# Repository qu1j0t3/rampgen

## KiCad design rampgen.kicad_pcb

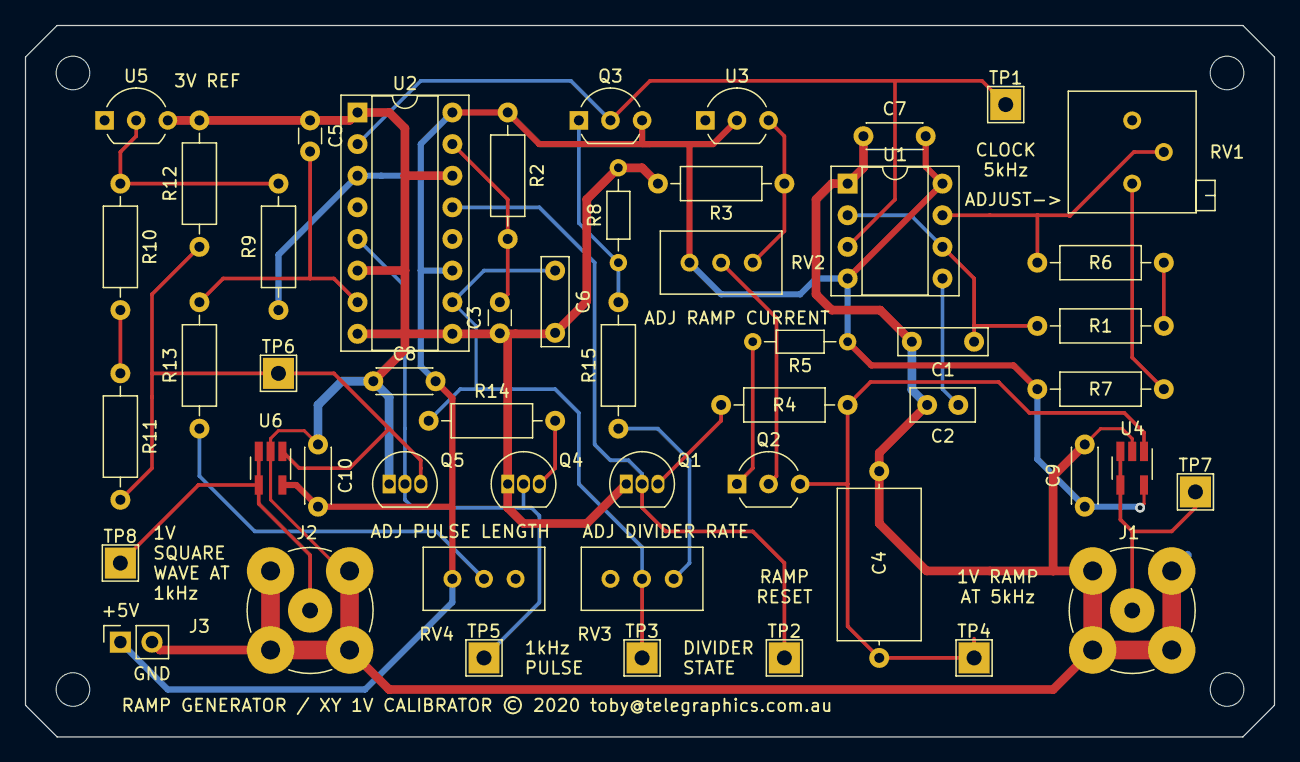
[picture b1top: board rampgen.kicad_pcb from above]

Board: 2 copper layers, 100.3 x 57.2 mm, 55 parts (0 on the bottom side), 27 nets.

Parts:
C1: 10n FILM; C_Rect_L7.0mm_W2.0mm_P5.00mm
C2: 100n; C_Disc_D5.0mm_W2.5mm_P2.50mm
C3, C5: 1n CER; C_Disc_D3.0mm_W1.6mm_P2.50mm
C4: 1.5n STYRENE; C_Axial_L12.0mm_D6.5mm_P15.00mm_Horizontal
C6: 100n FILM; C_Rect_L7.0mm_W2.0mm_P5.00mm
C7, C8, C9, C10: .01u; C_Disc_D4.3mm_W1.9mm_P5.00mm
H1, H2, H3, H4: MountingHole; MountingHole_2.7mm_M2.5
J1: RAMP_OUT; BNC_TEConnectivity_1478204_Vertical
J2: 1V_OUT; BNC_TEConnectivity_1478204_Vertical
J3: Conn_01x02_Female; PinSocket_1x02_P2.54mm_Vertical
Q1, Q4, Q5: 2N7000; TO-92_Inline
Q2: 2N3906; TO-92_Inline_Wide
Q3: 2N3904; TO-92_Inline_Wide
R1: 8.2k; R_Axial_DIN0207_L6.3mm_D2.5mm_P10.16mm_Horizontal
R2: 1k; R_Axial_DIN0207_L6.3mm_D2.5mm_P10.16mm_Horizontal
R3: 2.2k; R_Axial_DIN0207_L6.3mm_D2.5mm_P10.16mm_Horizontal
R4, R14: 47; R_Axial_DIN0207_L6.3mm_D2.5mm_P10.16mm_Horizontal
R5: 220k; R_Axial_DIN0204_L3.6mm_D1.6mm_P7.62mm_Horizontal
R6: 5.6k; R_Axial_DIN0207_L6.3mm_D2.5mm_P10.16mm_Horizontal
R7: 100; R_Axial_DIN0207_L6.3mm_D2.5mm_P10.16mm_Horizontal
R8: 100k; R_Axial_DIN0204_L3.6mm_D1.6mm_P7.62mm_Horizontal
R9: 4.7k; R_Axial_DIN0207_L6.3mm_D2.5mm_P10.16mm_Horizontal
R10, R11, R12, R13: 10k; R_Axial_DIN0207_L6.3mm_D2.5mm_P10.16mm_Horizontal
R15: 3.3k; R_Axial_DIN0207_L6.3mm_D2.5mm_P10.16mm_Horizontal
RV1: 1k; Potentiometer_Bourns_3299P_Horizontal
RV2, RV3: 10k; Potentiometer_Bourns_3296W_Vertical
RV4: 50k; Potentiometer_Bourns_3296W_Vertical
TP1: CLOCK; TestPoint_THTPad_2.5x2.5mm_Drill1.2mm
TP2: RAMP_RESET; TestPoint_THTPad_2.5x2.5mm_Drill1.2mm
TP3: DIVIDER; TestPoint_THTPad_2.5x2.5mm_Drill1.2mm
TP4: RAMP; TestPoint_THTPad_2.5x2.5mm_Drill1.2mm
TP5: DIV_RESET; TestPoint_THTPad_2.5x2.5mm_Drill1.2mm
TP6: 1V; TestPoint_THTPad_2.5x2.5mm_Drill1.2mm
TP7: RAMP_OUT; TestPoint_THTPad_2.5x2.5mm_Drill1.2mm
TP8: 1V_OUT; TestPoint_THTPad_2.5x2.5mm_Drill1.2mm
U1: NE555P; DIP-8_W7.62mm_Socket
U2: 74AHCT123; DIP-16_W7.62mm_Socket
U3, U5: LM4040LP-3; TO-92_Inline_Wide
U4, U6: MCP6001U; SOT-23-5_HandSoldering

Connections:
+5V: C7.2, C8.2, C9.2, C10.2, J3.1, Q3.3, R2.1, R5.1, R7.1, R9.1, RV2.1, RV4.1, U1.4, U1.8, U2.3, U2.11, U2.16, U3.2, U4.5, U6.5
GND: C1.2, C2.2, C3.1, C4.2, C5.1, C6.2, C7.1, C8.1, C9.1, C10.1, J1.2, J2.2, J3.2, Q1.1, Q4.1, Q5.1, R3.2, R8.2, R12.2, U1.1, U2.1, U2.6, U2.8, U2.9, U2.14, U4.2, U5.3, U6.2
unnamed: C1.1, R1.2, U1.2, U1.6
unnamed: C2.1, U1.5
unnamed: C3.2, R2.2, U2.15
unnamed: C4.1, Q2.3, R4.1, TP4.1, U4.1
unnamed: C5.2, R13.2, U2.7
unnamed: C6.1, R14.1, RV3.2, TP3.1, U2.10
unnamed: J1.1, TP7.1, U4.3, U4.4
unnamed: J2.1, TP8.1, U6.3, U6.4
unnamed: Q1.2, TP2.1, U2.13
unnamed: Q1.3, R4.2
unnamed: Q2.1, R5.2
unnamed: Q2.2, RV2.2
unnamed: Q3.1, R8.1, R15.2
unnamed: Q3.2, TP1.1, U1.3, U2.2
unnamed: Q4.2, Q5.2, TP5.1, U2.5
unnamed: Q4.3, R14.2
unnamed: Q5.3, R11.2, R12.1, TP6.1, U6.1
unnamed: R1.1, R6.2
unnamed: R3.1, RV2.3, U3.3
unnamed: R6.1, RV1.2, U1.7
unnamed: R7.2, RV1.1
unnamed: R9.2, R10.1, U5.2
unnamed: R10.2, R11.1
unnamed: R13.1, RV4.2
unnamed: R15.1, RV3.3

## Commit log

2020-11-22 Initial commit.
2020-11-23 Updated.
2022-07-10 Last changes but I don't recall exactly why.

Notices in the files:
rampgen.kicad_pcb:
RAMP GENERATOR / XY 1V CALIBRATOR © 2020 toby@telegraphics.com.au
